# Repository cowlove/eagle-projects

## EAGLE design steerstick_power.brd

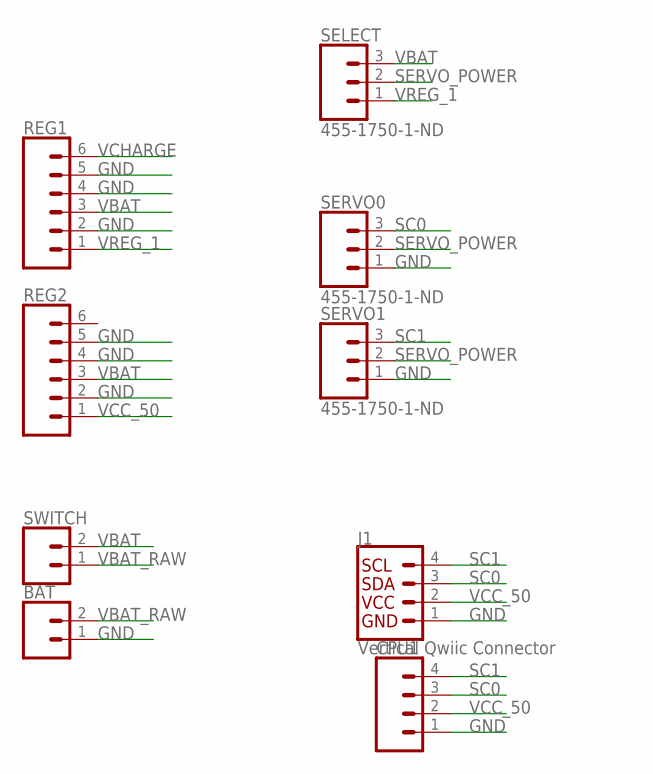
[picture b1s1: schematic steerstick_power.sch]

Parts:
BAT: CONN_02; 1X02
CPU1: CONN_041X04_NO_SILK; 1X04_NO_SILK
J1: Vertical Qwiic Connector; JST04_1MM_VERT
REG1, REG2: CONN_06SILK_FEMALE_PTH; 1X06
SELECT: 455-1750-1-ND; 1X03
SERVO0, SERVO1: 455-1750-1-ND; 1X03
SWITCH: CONN_02; 1X02

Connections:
GND: BAT.1, CPU1.1, J1.1, REG1.2, REG1.4, REG1.5, REG2.2, REG2.4, REG2.5, SERVO0.1, SERVO1.1
SC0: CPU1.3, J1.3, SERVO0.3
SC1: CPU1.4, J1.4, SERVO1.3
SERVO_POWER: SELECT.2, SERVO0.2, SERVO1.2
VBAT: REG1.3, REG2.3, SELECT.3, SWITCH.2
VBAT_RAW: BAT.2, SWITCH.1
VCC_50: CPU1.2, J1.2, REG2.1
VCHARGE: REG1.6
VREG_1: REG1.1, SELECT.1

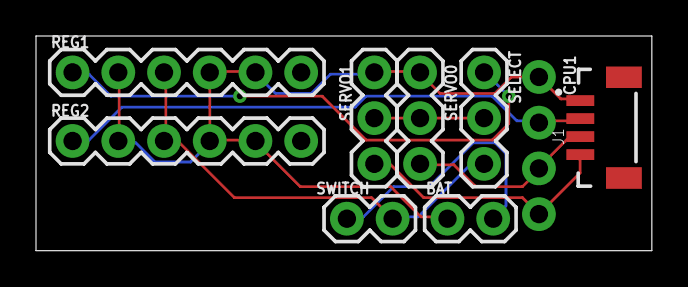
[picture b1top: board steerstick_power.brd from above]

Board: 2 copper layers, 34.2 x 11.9 mm, 9 parts (0 on the bottom side), 8 nets.

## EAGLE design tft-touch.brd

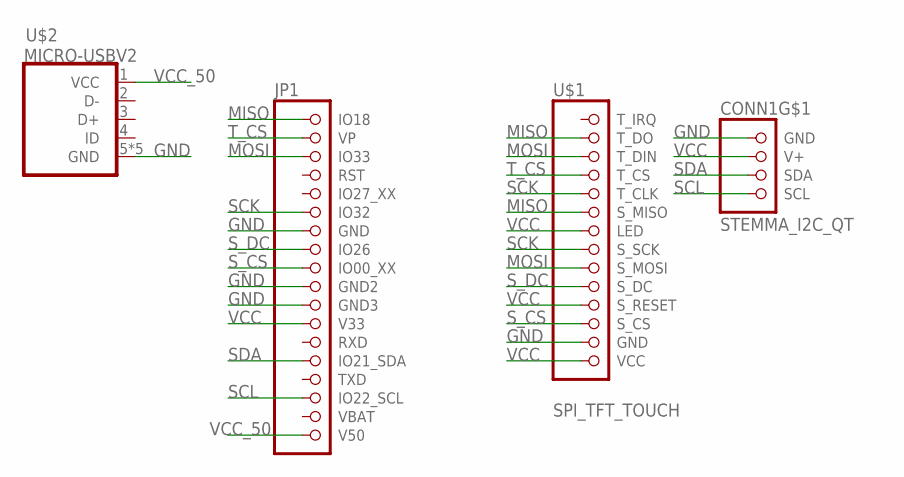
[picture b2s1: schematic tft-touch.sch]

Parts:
CONN1: STEMMA_I2C_QT; JST_SH4
JP1: TTGO-TS-ESP32; 00_2X9
U$1: SPI_TFT_TOUCH; 1X14_ROUND_70
U$2: MICRO-USBV2; MICRO-USB-2

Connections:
GND: CONN1.1 (GND), JP1.7 (GND), JP1.10 (GND2), JP1.11 (GND3), U$1.13 (GND), U$2.5 (GND), U$2.P$1 (GND), U$2.P$2 (GND), U$2.P$3 (GND), U$2.P$4 (GND)
MISO: JP1.1 (IO18), U$1.2 (T_DO), U$1.6 (S_MISO)
MOSI: JP1.3 (IO33), U$1.3 (T_DIN), U$1.9 (S_MOSI)
SCK: JP1.6 (IO32), U$1.5 (T_CLK), U$1.8 (S_SCK)
SCL: CONN1.4 (SCL), JP1.16 (IO22_SCL)
SDA: CONN1.3 (SDA), JP1.14 (IO21_SDA)
S_CS: JP1.9 (IO00_XX), U$1.12 (S_CS)
S_DC: JP1.8 (IO26), U$1.10 (S_DC)
T_CS: JP1.2 (VP), U$1.4 (T_CS)
VCC: CONN1.2 (V+), JP1.12 (V33), U$1.7 (LED), U$1.11 (S_RESET), U$1.14 (VCC)
VCC_50: JP1.18 (V50), U$2.1 (VCC)

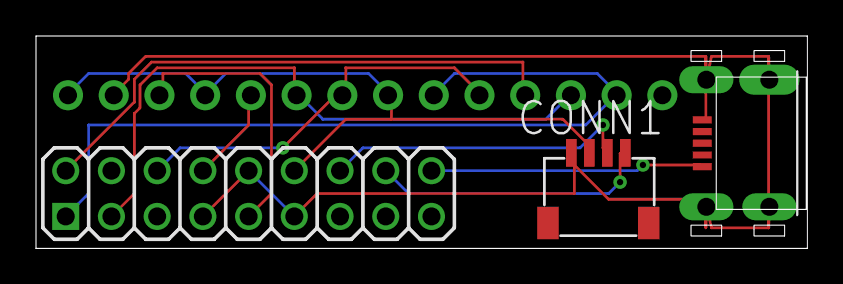
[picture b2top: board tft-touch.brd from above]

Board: 2 copper layers, 42.8 x 11.8 mm, 4 parts (0 on the bottom side), 11 nets.

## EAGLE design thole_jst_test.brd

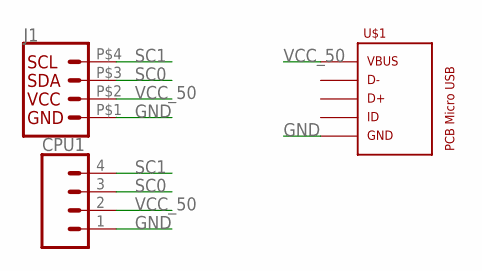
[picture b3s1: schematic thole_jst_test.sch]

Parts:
CPU1: CONN_041X04_NO_SILK; 1X04_NO_SILK
J1: Vertical Qwiic Connector; JST04_1MM_HOLES
U$1: PCB_MICRO_USB_BSS_2; USB_TYPE_B_SS_2

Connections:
GND: CPU1.1, J1.P$1 (1), U$1.5
SC0: CPU1.3, J1.P$3 (3)
SC1: CPU1.4, J1.P$4 (4)
VCC_50: CPU1.2, J1.P$2 (2), U$1.1

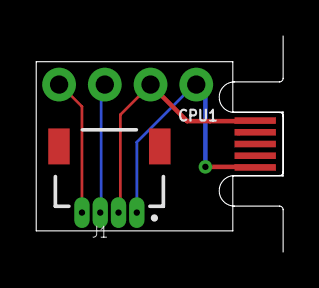
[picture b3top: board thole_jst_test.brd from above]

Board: 2 copper layers, 13.7 x 9.4 mm, 3 parts (0 on the bottom side), 4 nets.

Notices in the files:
parts and their libraries:
SparkFun-Connectors: Licensing: Creative Commons ShareAlike 4.0 International - https://creativecommons.org/licenses/by-sa/4.0
